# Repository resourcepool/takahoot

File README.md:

# Takahoot - Targets for Kahoot Games

V1:  

V2:  

## What is Kahoot?

Kahoot is this very cool tool to create quizzes and trivia for educational (or any other) purposes.  
Once the admin has setup all the questions, any player can just join the game and answer using a phone or any device that has a decent browser.

## What is Takahoot?
Well, we love Kahoot, we just thought that a phone was too "common" of a device to be fun.
So we made a target and bought nerf guns to replace it and answer all the questions while shooting.  
Simple enough isn't it?

Although this may seem **easy**, it actually means that we:
 * Conceived and Modelized every piece in 3D
 * Used 3D printers to print some of the parts
 * Used Laser-cutting machines to create the rest of the parts
 * Found and assembled the right electronics and sensors
 * Created an Arduino software + binary serial protocol to handle target-logic
 * Developed the main software UI to launch and control the games from your computer

We are very proud of this project and hope it can be useful to create a more ludic way of learning.

## Getting started guide

Already have your own targets? [Get started here](https://resourcepool.github.io/takahoot).

## Maker guide
Want to create your own device from scratch? [Follow the guide](https://resourcepool.github.io/takahoot).

Don't want to bother buying and printing / cutting materials?  
[Contact-us](mailto:loic@takima.fr) and we will find a way to do that for you and send you the whole kits ready to assemble.

## Contributors

A big Thanks to [Takima](https://www.takima.fr) who sponsored us and invested much time and efforts into helping to make this project a reality.  

Thanks to the lead contributors of the project:  
 * [Loïc Ortola](https://github.com/loicortola) - Original author, target design & making, Hardware & Arduino
 * [Alexandre Nunesse](https://github.com/anunesse) - Kahoot API, Target fixes & Takahoot Client
 * [Logan Lepage](https://github.com/loganlepage) - Takahoot UI & Client

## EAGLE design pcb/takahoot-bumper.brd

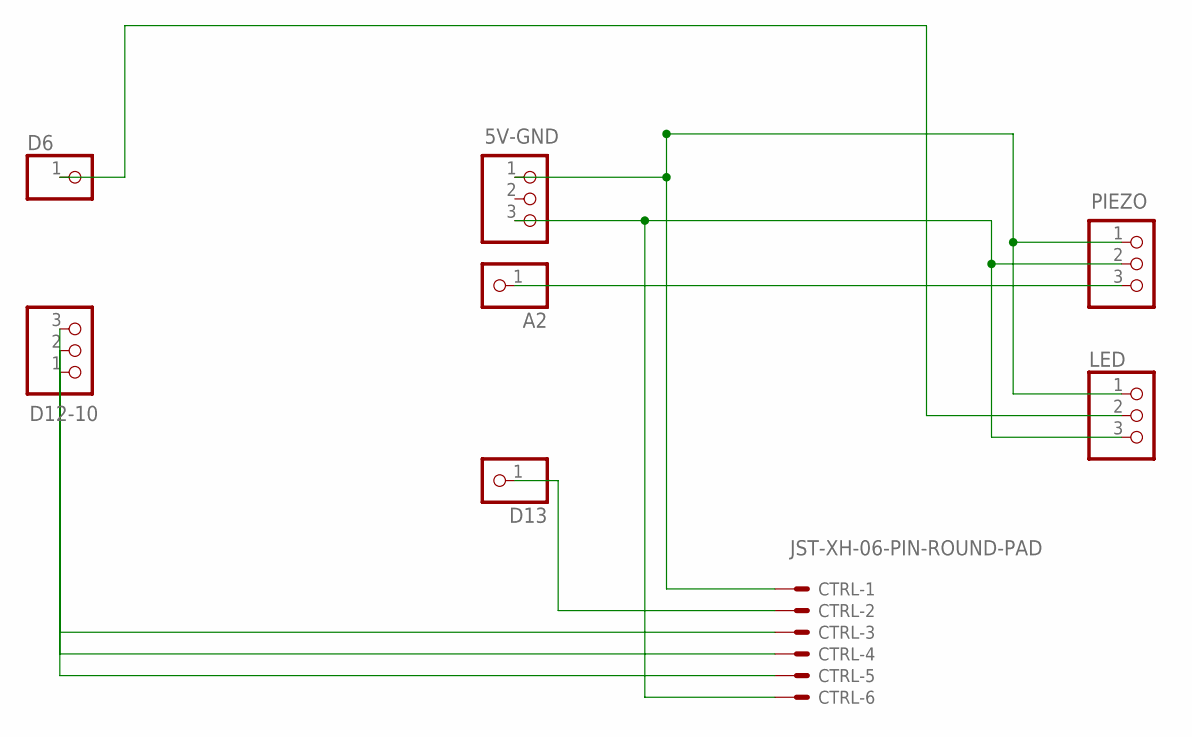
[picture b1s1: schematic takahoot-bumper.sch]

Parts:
5V-GND: PINHD-1X3; 1X03
A2: PINHD-1X1; 1X01
CTRL: JST-XH-06-PIN-ROUND-PAD; JST-XH-06-PACKAGE-ROUND-PAD
D6, D13: PINHD-1X1; 1X01
D12-10: PINHD-1X3; 1X03
LED: PINHD-1X3/90; 1X03/90
PIEZO: PINHD-1X3/90; 1X03/90

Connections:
unnamed: CTRL.5, D12-10.1
unnamed: CTRL.4, D12-10.2
unnamed: CTRL.3, D12-10.3
unnamed: CTRL.2, D13.1
unnamed: 5V-GND.3, CTRL.6, LED.3, PIEZO.2
unnamed: 5V-GND.1, CTRL.1, LED.1, PIEZO.1
unnamed: A2.1, PIEZO.3
unnamed: D6.1, LED.2

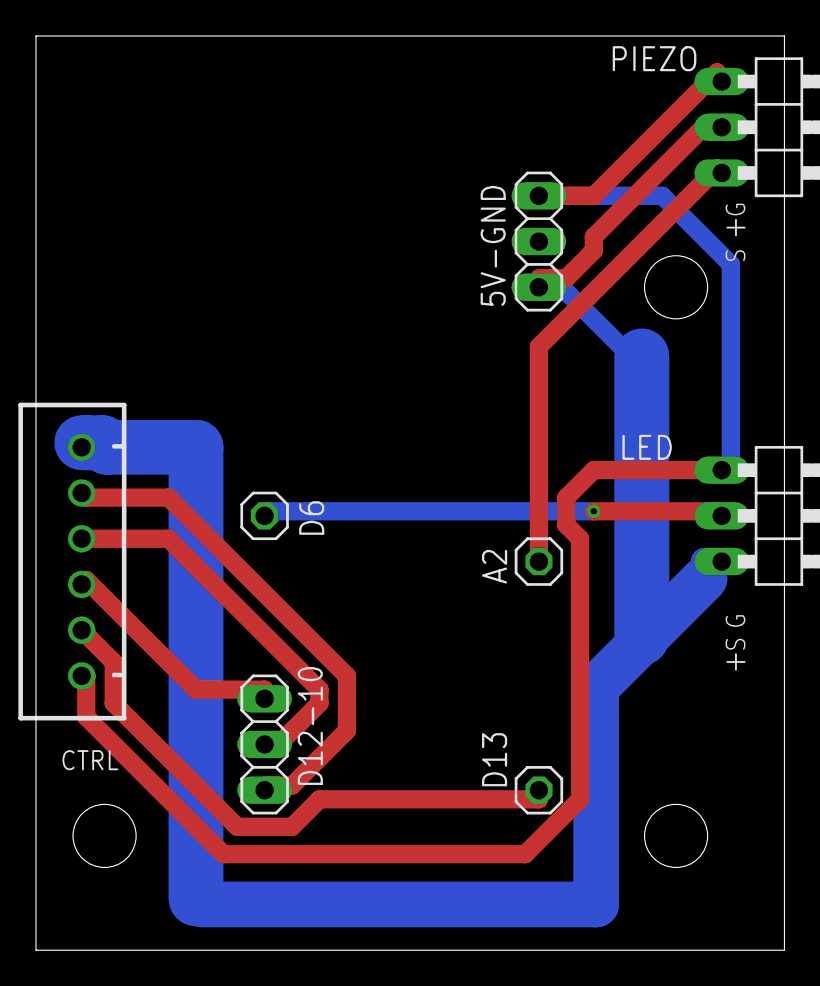
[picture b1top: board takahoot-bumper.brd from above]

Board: 2 copper layers, 41.6 x 50.8 mm, 8 parts (0 on the bottom side), 8 nets.

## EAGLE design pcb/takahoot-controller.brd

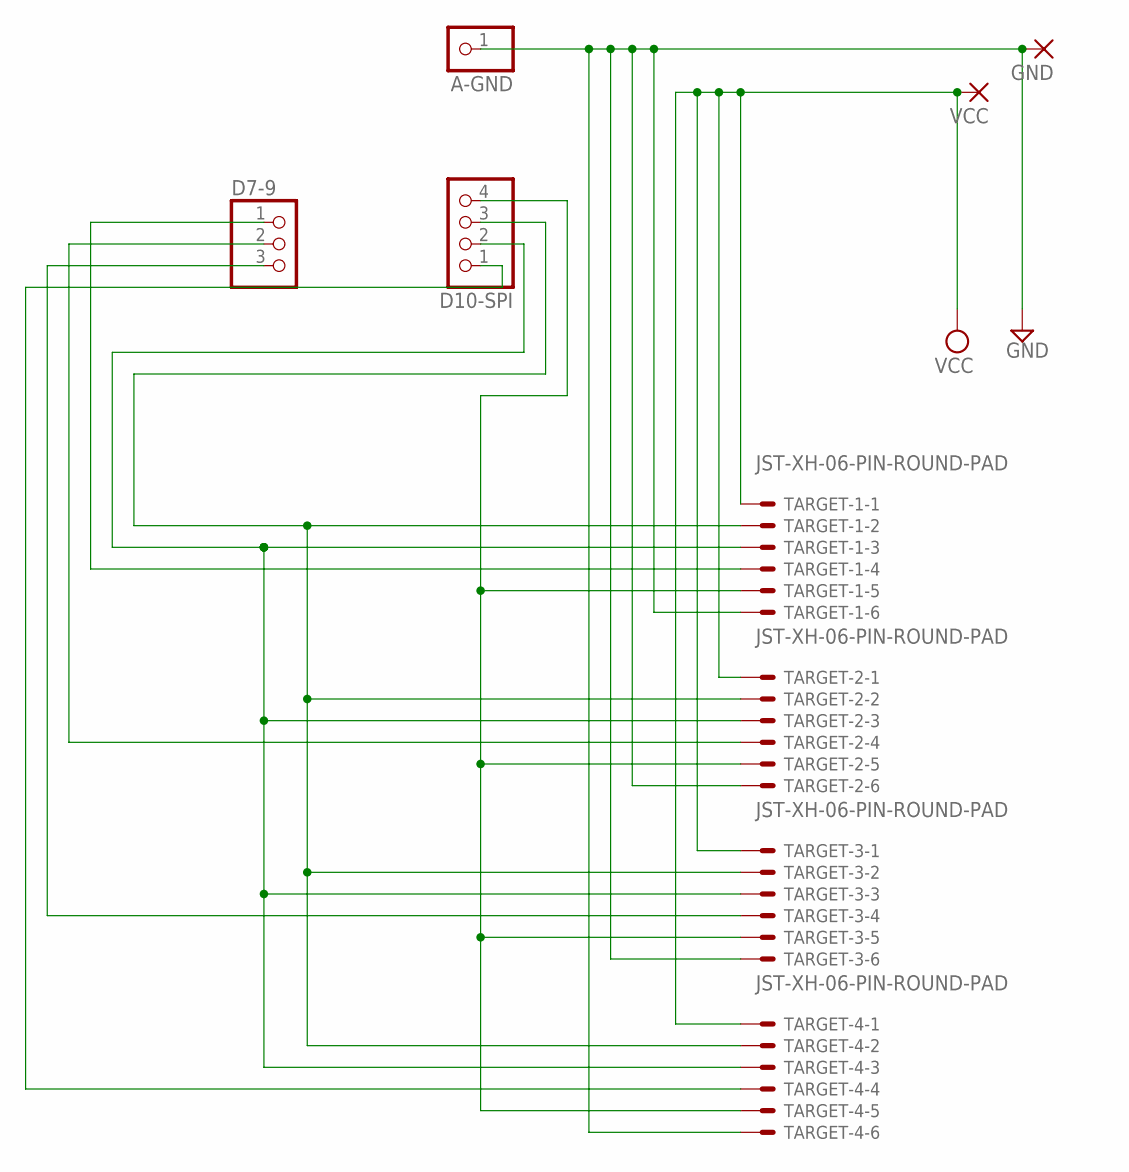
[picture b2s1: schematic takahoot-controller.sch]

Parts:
A-GND: PINHD-1X1; 1X01
D7-9: PINHD-1X3; 1X03
D10-SPI: PINHD-1X4; 1X04
GND: 3,81/1,4
TARGET-1, TARGET-2, TARGET-3, TARGET-4: JST-XH-06-PIN-ROUND-PAD; JST-XH-06-PACKAGE-ROUND-PAD
VCC: 3,81/1,4

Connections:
GND: A-GND.1, GND.1, TARGET-1.6, TARGET-2.6, TARGET-3.6, TARGET-4.6
MISO: D10-SPI.3, TARGET-1.2, TARGET-2.2, TARGET-3.2, TARGET-4.2
MOSI: D10-SPI.2, TARGET-1.3, TARGET-2.3, TARGET-3.3, TARGET-4.3
SCK: D10-SPI.4, TARGET-1.5, TARGET-2.5, TARGET-3.5, TARGET-4.5
SS1: D7-9.1, TARGET-1.4
SS2: D7-9.2, TARGET-2.4
SS3: D7-9.3, TARGET-3.4
SS4: D10-SPI.1, TARGET-4.4
VCC: TARGET-1.1, TARGET-2.1, TARGET-3.1, TARGET-4.1, VCC.1

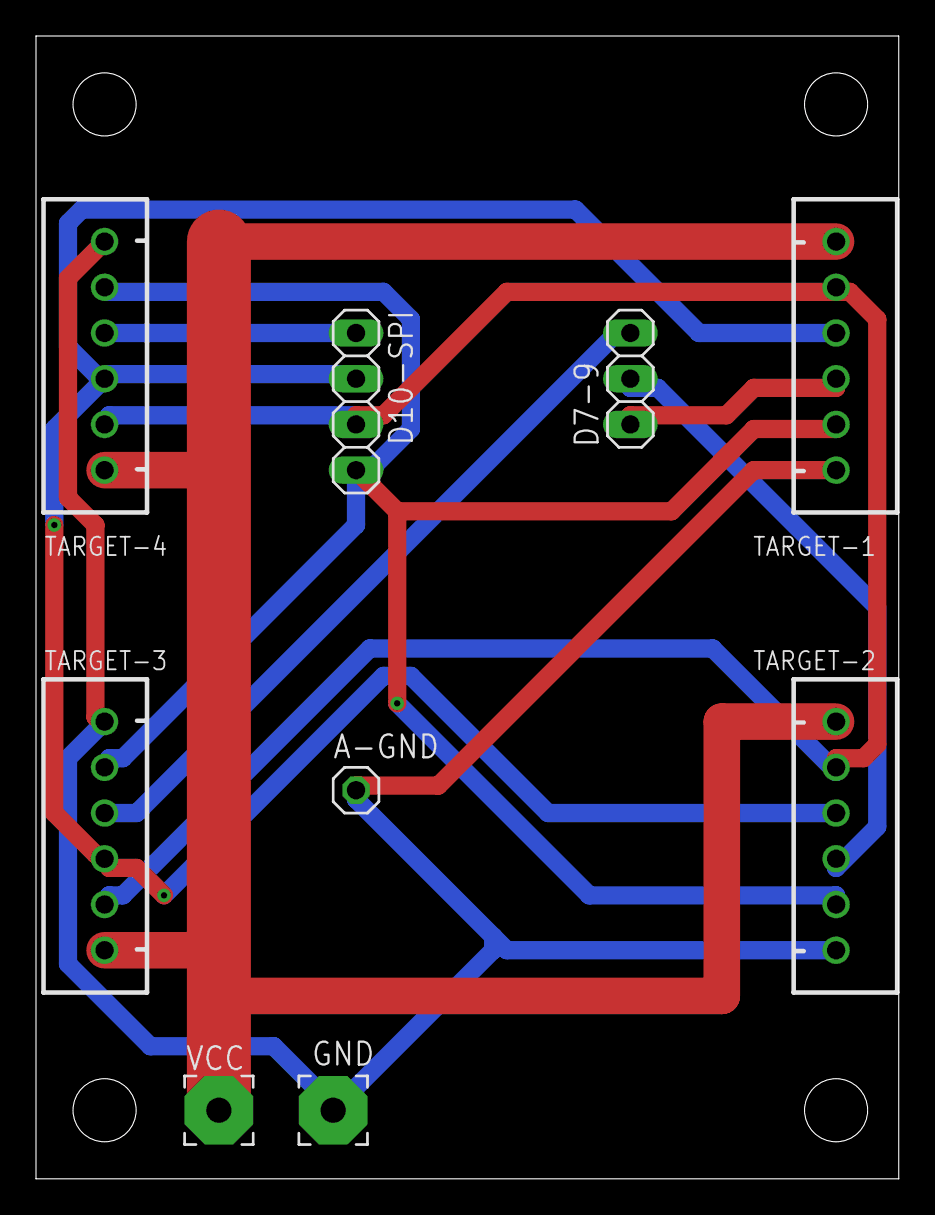
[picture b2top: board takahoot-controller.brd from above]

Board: 2 copper layers, 47.9 x 63.5 mm, 9 parts (0 on the bottom side), 9 nets.

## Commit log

2019-02-09 Added codebase
2019-02-09 Implemented Arduino commands and Serial protocol
2019-02-09 Added node codebase
2019-02-10 Now plugged in whole circuitry. It works.
2019-02-10 Fixed issues with logging & empty sensor
2019-03-01 Add basic express server
2019-03-01 ajout client, 'ng serve' to run
2019-03-01 add files inside client/ folder
2019-03-01 add Start the game button
2019-03-01 Save winston & init on server start
2019-03-03 client : replace angular by vuejs
2019-03-04 Changed protocol to add calibration command
2019-03-04 update client UI
2019-03-04 fix packaging client prod
2019-03-04 add 'Arduino LLC (www.arduino.cc)' manufacurer to target-service port
2019-03-04 server: delete unused code
2019-03-05 Rebuild on install
2019-03-05 play button disabled if targets are not configured
2019-03-05 test worker targets
2019-03-06 loader-worker
2019-03-06 serial port utils workers bridged
2019-03-07 redux implemented with our app
2019-03-08 Create kahoot simple object
2019-03-08 Add steps to configuration
2019-03-09 Connect to kahoot
2019-03-11 pairing & calibration
2019-03-13 refacto actions
2019-03-14 ajout game reset après calibration
2019-03-14 refacto event listeners with switch
2019-03-14 Add KahootGame
2019-03-14 refacto
2019-03-15 Bind hit to answer
2019-03-15 fix actions and bind hit
2019-03-15 add start vue
2019-03-15 style start.vue
2019-03-19 Set game pin properly
2019-03-19 Use real user agent for kahoot API
2019-03-19 Fix set player name
2019-03-19 Clean properly onEnd
2019-03-19 Reset on question start
2019-03-19 Add End view and clean button
2019-03-21 Add testing step (post calibration)
2019-03-21 project packageable : npm run package, then go to ./builds/takahoot[...]/
2019-03-21 ajout packages linux et mac
2019-03-28 Fix test step
2019-03-29 Add target hit img
2019-03-29 Fix versions
2019-03-29 Order players properly
2019-04-01 Fix undefined devices and adjust pairing
2019-04-04 Fixed config
2019-04-05 Implemented led controller change
2019-04-05 Fixed import
2019-04-05 Recalibrate on quizz end
2019-04-05 Player 1 to 4
2019-04-11 Add simple fr doc
2019-04-12 Fix doc
2019-04-18 fix weak network issues
2019-05-21 Clean build, set version to1.9 and add icon
2019-05-21 Release 0.9.0
2019-05-21 Added docs boilerplate, and deploy_docs script
2019-11-14 Arduino Takahoot v2
2019-12-02 Tutorial build guide WIP
2019-12-09 Updated target tutorial
2019-12-10 Finished tutorial
2020-01-14 Added support for WebUSB
2020-01-16 Cleaned config
2020-02-06 Exported WebUSB config
2020-02-06 webusb client, self signed ssl
2020-02-06 Fixed PEM
2020-02-06 Refactored simulator
2020-02-06 Fixed web
2020-02-06 Fixed stuff
2020-02-14 Remove takahoot electron client
2020-02-14 Remove old bridge & common modules
2020-02-14 Simple Web USB client
2020-02-17 Add bumper
2020-02-17 Clean & kahoot connect #1
2020-02-17 Clean & kahoot connect #2
2020-02-19 Add calibration input
2020-02-19 Add calibrate and enable all
2020-02-19 Add disable all
2020-02-19 Fixes
2020-03-03 adding sensibility to print
2020-03-04 fix sendTolerance
2020-03-04 Added angular boilerplate
2020-03-04 Added basic working I/O
2020-03-05 Finished boilerplate
2020-03-05 Renamed target to bumper
2020-03-05 Refactored hierarchy
2020-03-05 Modified gitignore
2020-03-06 adding doc for uploading controller
2020-03-12 ajout bouton select Device
2020-03-12 WIP select devices : call the service
2020-03-12 Feat selectDevices Button
2020-05-05 Updated docs
2020-05-05 Fixed dead link
2020-05-05 Added PCB
2022-02-11 Bump karma from 4.4.1 to 6.3.14 in /www
    Bumps [karma](https://github.com/karma-runner/karma) from 4.4.1 to 6.3.14.
    - [Release notes](https://github.com/karma-runner/karma/releases)
    - [Changelog](https://github.com/karma-runner/karma/blob/master/CHANGELOG.md)
    - [Commits](https://github.com/karma-runner/karma/compare/v4.4.1...v6.3.14)
    ---
    updated-dependencies:
2022-03-02 Bump karma from 4.4.1 to 6.3.16 in /www
    Bumps [karma](https://github.com/karma-runner/karma) from 4.4.1 to 6.3.16.
    - [Release notes](https://github.com/karma-runner/karma/releases)
    - [Changelog](https://github.com/karma-runner/karma/blob/master/CHANGELOG.md)
    - [Commits](https://github.com/karma-runner/karma/compare/v4.4.1...v6.3.16)
    ---
    updated-dependencies:
2022-06-03 Bump @angular/core from 9.0.4 to 11.0.5 in /www
    Bumps [@angular/core](https://github.com/angular/angular/tree/HEAD/packages/core) from 9.0.4 to 11.0.5.
    - [Release notes](https://github.com/angular/angular/releases)
    - [Changelog](https://github.com/angular/angular/blob/main/CHANGELOG.md)
    - [Commits](https://github.com/angular/angular/commits/11.0.5/packages/core)
    ---
    updated-dependencies:
2023-04-30 Bump jszip from 3.2.2 to 3.10.1 in /www
    Bumps [jszip](https://github.com/Stuk/jszip) from 3.2.2 to 3.10.1.
    - [Release notes](https://github.com/Stuk/jszip/releases)
    - [Changelog](https://github.com/Stuk/jszip/blob/main/CHANGES.md)
    - [Commits](https://github.com/Stuk/jszip/compare/v3.2.2...v3.10.1)
    ---
    updated-dependencies:
2023-04-30 Bump decode-uri-component from 0.2.0 to 0.2.2 in /www
    Bumps [decode-uri-component](https://github.com/SamVerschueren/decode-uri-component) from 0.2.0 to 0.2.2.
    - [Release notes](https://github.com/SamVerschueren/decode-uri-component/releases)
    - [Commits](https://github.com/SamVerschueren/decode-uri-component/compare/v0.2.0...v0.2.2)
    ---
    updated-dependencies:
    - dependency-name: decode-uri-component
2023-04-30 Bump qs from 6.5.2 to 6.5.3 in /www
    Bumps [qs](https://github.com/ljharb/qs) from 6.5.2 to 6.5.3.
    - [Release notes](https://github.com/ljharb/qs/releases)
    - [Changelog](https://github.com/ljharb/qs/blob/main/CHANGELOG.md)
    - [Commits](https://github.com/ljharb/qs/compare/v6.5.2...v6.5.3)
    ---
    updated-dependencies:
2023-04-30 Bump json5 from 1.0.1 to 1.0.2 in /www
    Bumps [json5](https://github.com/json5/json5) from 1.0.1 to 1.0.2.
    - [Release notes](https://github.com/json5/json5/releases)
    - [Changelog](https://github.com/json5/json5/blob/main/CHANGELOG.md)
    - [Commits](https://github.com/json5/json5/compare/v1.0.1...v1.0.2)
    ---
    updated-dependencies:
2023-04-30 Bump http-cache-semantics and @angular/cli in /www
    Bumps [http-cache-semantics](https://github.com/kornelski/http-cache-semantics) to 4.1.1 and updates ancestor dependency [@angular/cli](https://github.com/angular/angular-cli). These dependencies nee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
    Updates `http-cache-semantics` from 3.8.1 to 4.1.1
    - [Release notes](https://github.com/kornelski/http-cache-semantics/releases)
    - [Commits](https://github.com/kornelski/http-cache-semantics/compare/v3.8.1...v4.1.1)
    Updates `@angular/cli` from 9.0.4 to 9.1.0
    - [Release notes](https://github.com/angular/angular-cli/releases)
2023-04-30 Bump minimist, mkdirp, karma and protractor in /www
    Bumps [minimist](https://github.com/minimistjs/minimist) to 1.2.8 and updates ancestor dependencies [minimist](https://github.com/minimistjs/minimist), [mkdirp](https://github.com/isaacs/node-mkdirp)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
    Updates `minimist` from 1.2.0 to 1.2.8
    - [Release notes](https://github.com/minimistjs/minimist/releases)
    - [Changelog](https://github.com/minimistjs/minimist/blob/main/CHANGELOG.md)
    - [Commits](https://github.com/minimistjs/minimist/compare/v1.2.0...v1.2.8)
    Updates `mkdirp` from 0.5.1 to 0.
2026-04-03 Update contributor acknowledgments in README
